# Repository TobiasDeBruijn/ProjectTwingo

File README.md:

# Project Twingo
I own a Renault Twingo Initiale from 2002. This car originally shipped with a simple FM radio, that wasn't enough.

## Goals
With this project I'm trying to do the following:
- Add Android Auto to the Twingo, both wireless and via USB
    - Retain the steering wheel controls
- Interior lighting
    - Replace ceiling light with LED
    - Feet of front passengers
- Replace the standard display in the middle of the dashboard? (Mine is sortof broken)
- Control AC electronically with a thermostat?

## License
All work in this project is licensed under the MIT license.

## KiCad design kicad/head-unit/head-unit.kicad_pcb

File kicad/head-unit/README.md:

# Head unit
The 'head unit' and all the required additional stuff

## head-unit
This is the main bit of the unit. This contains the STM32 microcontroller, the Raspberry Pi running Android Auto, the DAC and various controlling relays.

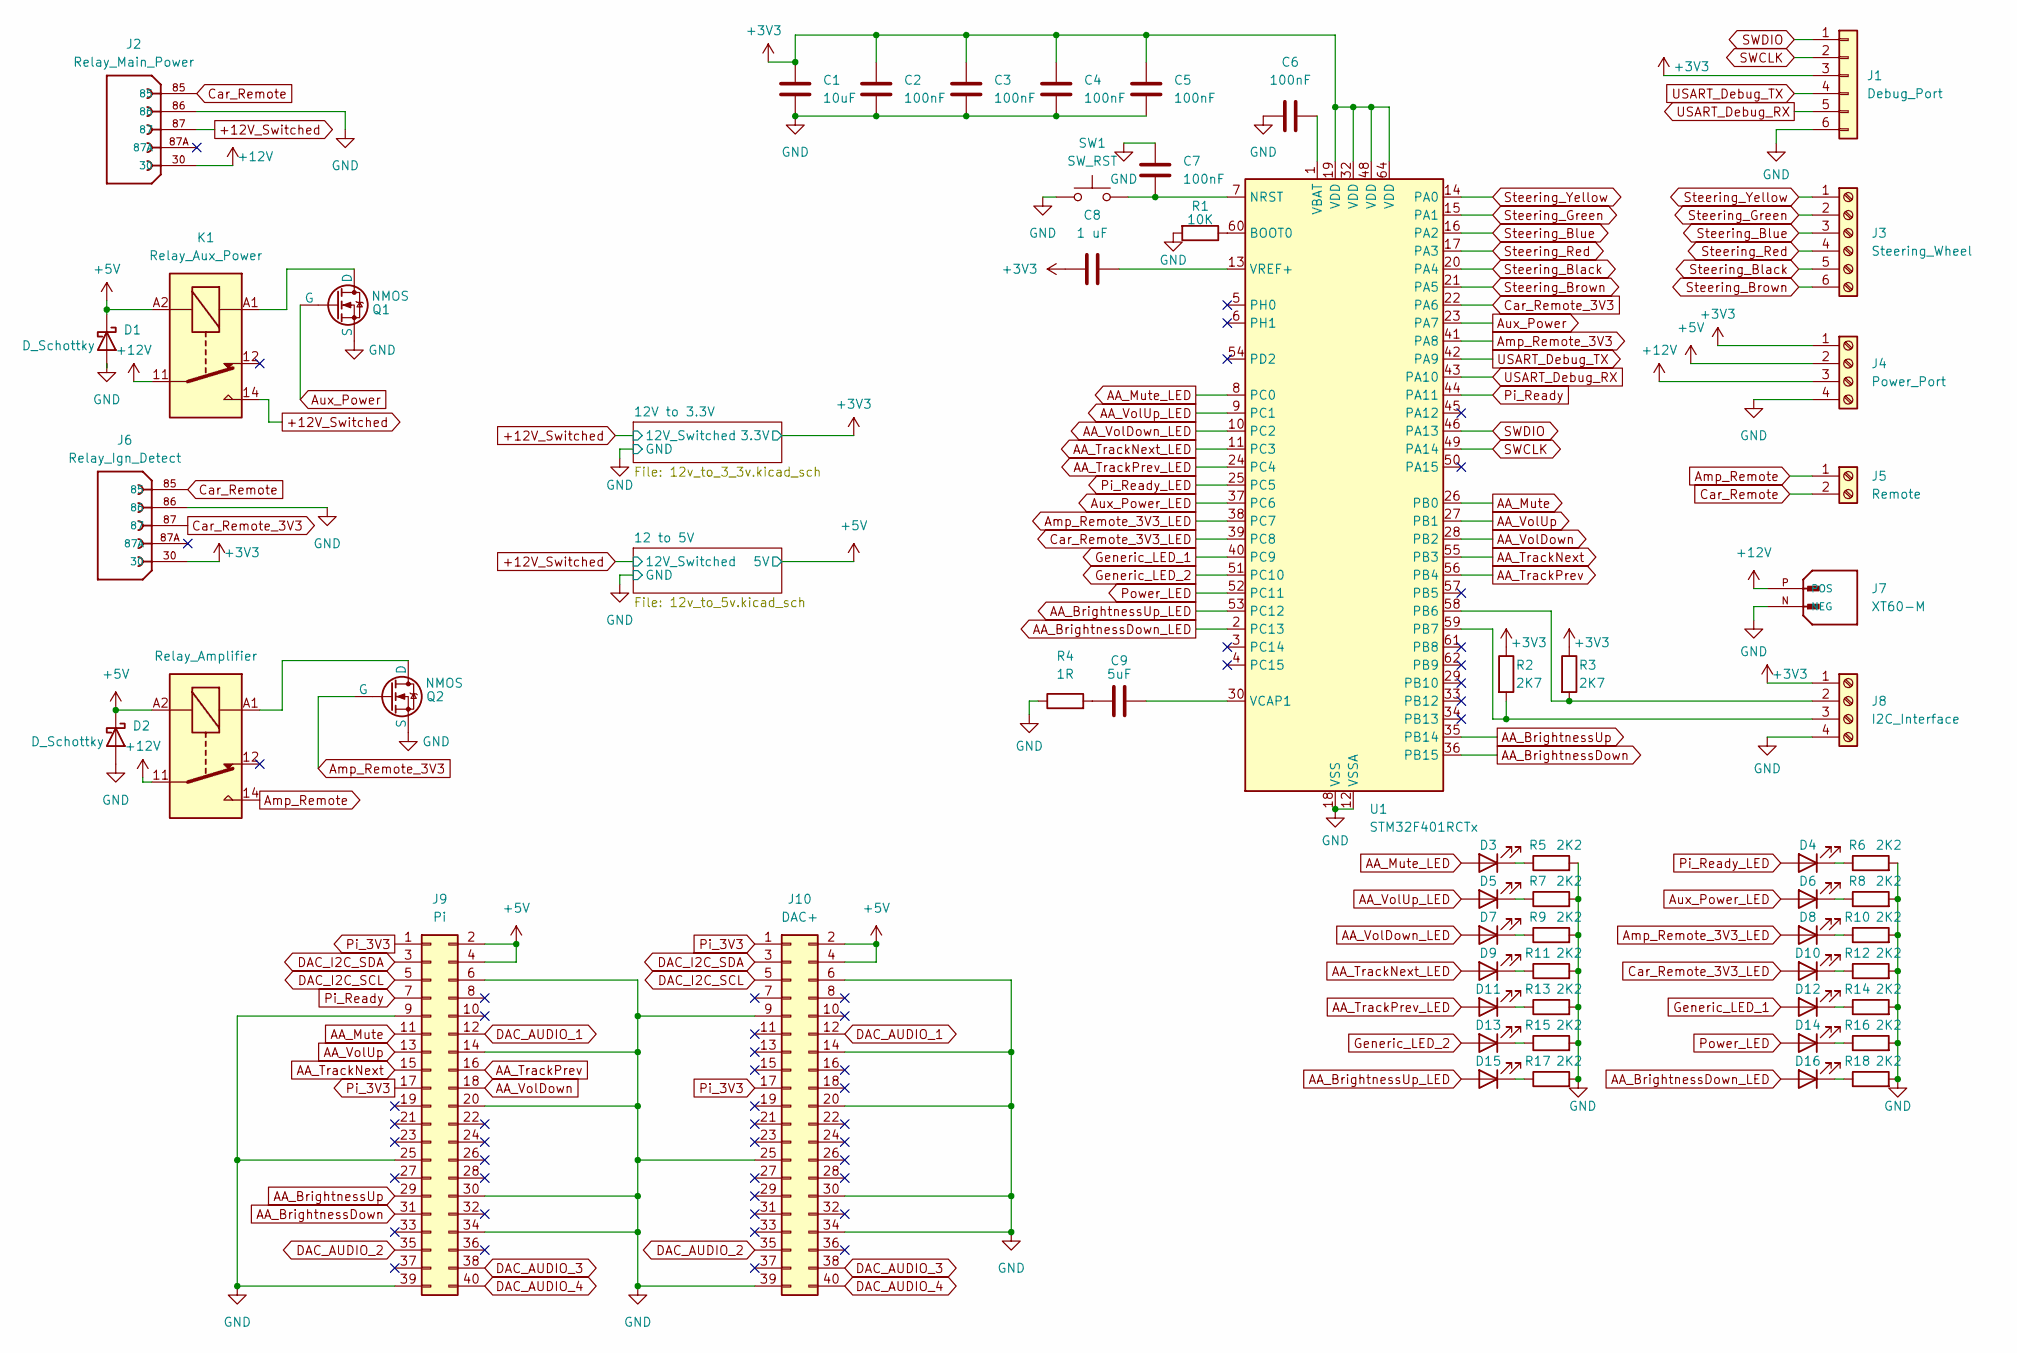
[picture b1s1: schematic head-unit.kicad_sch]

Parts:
C1: 10uF; C_0603_1608Metric
C2, C3, C4, C5, C6, C7: 100nF; C_0402_1005Metric
C8: 1 uF; C_0402_1005Metric
C9: 5uF; C_0603_1608Metric
D1, D2: D_Schottky; D_0603_1608Metric
D3, D4, D5, D6, D7, D8, D9, D10, D11, D12, D13, D14, D15, D16: LED; LED_0603_1608Metric
J1: Debug_Port; PinHeader_1x06_P2.54mm_Vertical
J2: Relay_Main_Power; TE_VCF4-1000; PARTREV B
J3: Steering_Wheel; TerminalBlock_bornier-6_P5.08mm
J4: Power_Port; TerminalBlock_bornier-4_P5.08mm
J5: Remote; TerminalBlock_bornier-2_P5.08mm
J6: Relay_Ign_Detect; TE_VCF4-1000; PARTREV B
J7: XT60-M; AMASS_XT60-M; PARTREV V1.2
J8: I2C_Interface; TerminalBlock_bornier-4_P5.08mm
J9: Pi; PinHeader_2x20_P2.54mm_Vertical
J10: DAC+; PinHeader_2x20_P2.54mm_Vertical
K1: Relay_Aux_Power; Relay_SPDT_Finder_36.11
K2: Relay_Amplifier; Relay_SPDT_Finder_36.11
Q1, Q2: NMOS; SW_SPDT_CK-JS102011SAQN
R1: 10K; R_0603_1608Metric
R2, R3: 2K7; R_0402_1005Metric
R4: 1R; R_0402_1005Metric
R5, R6, R7, R8, R9, R10, R11, R12, R13, R14, R15, R16, R17, R18: 2K2; R_0402_1005Metric
SW1: SW_RST; SW_Push_1P1T_NO_CK_KSC7xxJ
U1: STM32F401RCTx; LQFP-64_10x10mm_P0.5mm

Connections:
+3V3: C1.1, C2.1, C3.1, C4.1, C5.1, C8.2, J1.3, J4.1, J6.30, J8.1, R2.1, R3.1, U1.19 (VDD), U1.32 (VDD), U1.48 (VDD), U1.64 (VDD); also elsewhere on the board
+5V: D1.1 (K), D2.1 (K), J4.2, J9.2, J9.4, J10.2, J10.4, K1.A2, K2.A2; also elsewhere on the board
+12V: J2.30, J4.3, J7.P (POS), K1.11, K2.11
+12V_Switched: J2.87, K1.14; also elsewhere on the board
AA_BrightnessDown: J9.31, U1.36 (PB15)
AA_BrightnessDown_LED: D16.2 (A), U1.2 (PC13)
AA_BrightnessUp: J9.29, U1.35 (PB14)
AA_BrightnessUp_LED: D15.2 (A), U1.53 (PC12)
AA_Mute: J9.11, U1.26 (PB0)
AA_Mute_LED: D3.2 (A), U1.8 (PC0)
AA_TrackNext: J9.15, U1.55 (PB3)
AA_TrackNext_LED: D9.2 (A), U1.11 (PC3)
AA_TrackPrev: J9.16, U1.56 (PB4)
AA_TrackPrev_LED: D11.2 (A), U1.24 (PC4)
AA_VolDown: J9.18, U1.28 (PB2)
AA_VolDown_LED: D7.2 (A), U1.10 (PC2)
AA_VolUp: J9.13, U1.27 (PB1)
AA_VolUp_LED: D5.2 (A), U1.9 (PC1)
Amp_Remote: J5.1, K2.14
Amp_Remote_3V3: Q2.2 (G), U1.41 (PA8)
Amp_Remote_3V3_LED: D8.2 (A), U1.38 (PC7)
Aux_Power: Q1.2 (G), U1.23 (PA7)
Aux_Power_LED: D6.2 (A), U1.37 (PC6)
Car_Remote: J2.85, J5.2, J6.85
Car_Remote_3V3: J6.87, U1.22 (PA6)
Car_Remote_3V3_LED: D10.2 (A), U1.39 (PC8)
DAC_AUDIO_1: J9.12, J10.12
DAC_AUDIO_2: J9.35, J10.35
DAC_AUDIO_3: J9.38, J10.38
DAC_AUDIO_4: J9.40, J10.40
DAC_I2C_SCL: J9.5, J10.5
DAC_I2C_SDA: J9.3, J10.3
GND: C1.2, C2.2, C3.2, C4.2, C5.2, C6.1, C7.1, D1.2 (A), D2.2 (A), J1.6, J2.86, J4.4, J6.86, J7.N (NEG), J8.4, J9.6, J9.9, J9.14, J9.20, J9.25, J9.30, J9.34, J9.39, J10.6, J10.9, J10.14, J10.20, J10.25, J10.30, J10.34, J10.39, Q1.3 (S), Q2.3 (S), R1.2, R4.1, R5.2, R6.2, R7.2, R8.2, R9.2, R10.2, R11.2, R12.2, R13.2, R14.2, R15.2, R16.2, R17.2, R18.2, SW1.1, U1.12 (VSSA), U1.18 (VSS), U1.31 (VSS), U1.47 (VSS), U1.63 (VSS); also elsewhere on the board
Generic_LED_1: D12.2 (A), U1.40 (PC9)
Generic_LED_2: D13.2 (A), U1.51 (PC10)
unnamed: C9.2, R4.2
unnamed: D3.1 (K), R5.1
unnamed: D4.1 (K), R6.1
unnamed: D5.1 (K), R7.1
unnamed: D6.1 (K), R8.1
unnamed: D7.1 (K), R9.1
unnamed: D8.1 (K), R10.1
unnamed: D9.1 (K), R11.1
unnamed: D10.1 (K), R12.1
unnamed: D11.1 (K), R13.1
unnamed: D12.1 (K), R14.1
unnamed: D13.1 (K), R15.1
unnamed: D14.1 (K), R16.1
unnamed: D15.1 (K), R17.1
unnamed: D16.1 (K), R18.1
unnamed: J8.2, R3.2, U1.58 (PB6)
unnamed: J8.3, R2.2, U1.59 (PB7)
unnamed: K1.A1, Q1.1 (D)
unnamed: K2.A1, Q2.1 (D)
unnamed: R1.1, U1.60 (BOOT0)
unnamed: C7.2, SW1.2, U1.7 (NRST)
unnamed: C6.2, U1.1 (VBAT)
unnamed: C9.1, U1.30 (VCAP1)
unnamed: C8.1, U1.13 (VREF+)
Pi_3V3: J9.1, J9.17, J10.1, J10.17
Pi_Ready: J9.7, U1.44 (PA11)
Pi_Ready_LED: D4.2 (A), U1.25 (PC5)
Power_LED: D14.2 (A), U1.52 (PC11)
SWCLK: J1.2, U1.49 (PA14)
SWDIO: J1.1, U1.46 (PA13)
Steering_Black: J3.5, U1.20 (PA4)
Steering_Blue: J3.3, U1.16 (PA2)
Steering_Brown: J3.6, U1.21 (PA5)
Steering_Green: J3.2, U1.15 (PA1)
Steering_Red: J3.4, U1.17 (PA3)
Steering_Yellow: J3.1, U1.14 (PA0)
USART_Debug_RX: J1.5, U1.43 (PA10)
USART_Debug_TX: J1.4, U1.42 (PA9)

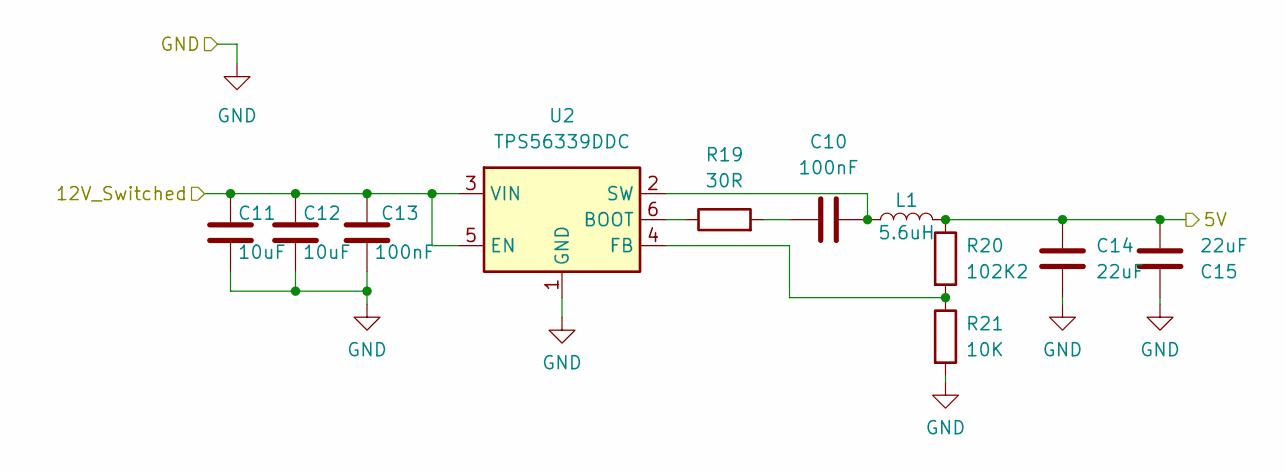
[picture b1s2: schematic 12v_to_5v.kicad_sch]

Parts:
C10, C13: 100nF; C_0402_1005Metric
C11, C12: 10uF; C_0603_1608Metric
C14, C15: 22uF; C_0603_1608Metric
L1: 5.6uH; L_6.3x6.3_H3
R19: 30R; R_0201_0603Metric
R20: 102K2; R_0805_2012Metric
R21: 10K; R_0603_1608Metric
U2: TPS56339DDC; SOT-23-6

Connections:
+5V: C14.1, C15.2, L1.2, R20.1; also elsewhere on the board
+12V_Switched: C11.1, C12.1, C13.1, U2.3 (VIN), U2.5 (EN); also elsewhere on the board
GND: C11.2, C12.2, C13.2, C14.2, C15.1, R21.2, U2.1 (GND); also elsewhere on the board
unnamed: C10.1, R19.2
unnamed: R19.1, U2.6 (BOOT)
unnamed: R20.2, R21.1, U2.4 (FB)
unnamed: C10.2, L1.1, U2.2 (SW)

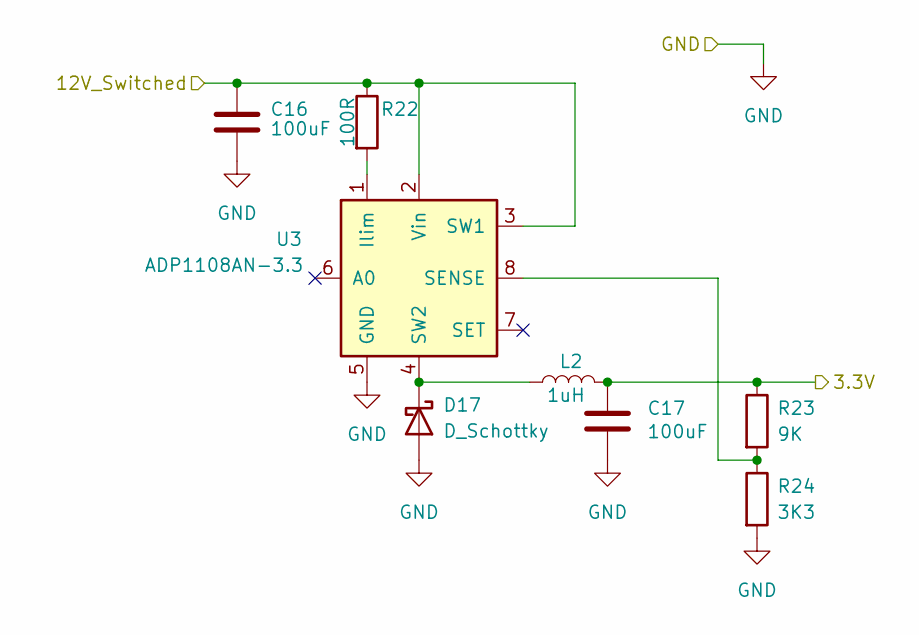
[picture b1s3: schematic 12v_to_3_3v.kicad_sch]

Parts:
C16, C17: 100uF; C_1206_3216Metric
D17: D_Schottky; D_0603_1608Metric
L2: 1uH; L_0402_1005Metric
R22: 100R; R_0402_1005Metric
R23: 9K; R_0603_1608Metric
R24: 3K3; R_0603_1608Metric
U3: ADP1108AN-3.3; DIP-8_W7.62mm

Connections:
+3V3: C17.1, L2.2, R23.1; also elsewhere on the board
+12V_Switched: C16.1, R22.1, U3.2 (Vin), U3.3 (SW1); also elsewhere on the board
GND: C16.2, C17.2, D17.2 (A), R24.2, U3.5 (GND); also elsewhere on the board
unnamed: D17.1 (K), L2.1, U3.4 (SW2)
unnamed: R22.2, U3.1 (Ilim)
unnamed: R23.2, R24.1, U3.8 (SENSE)

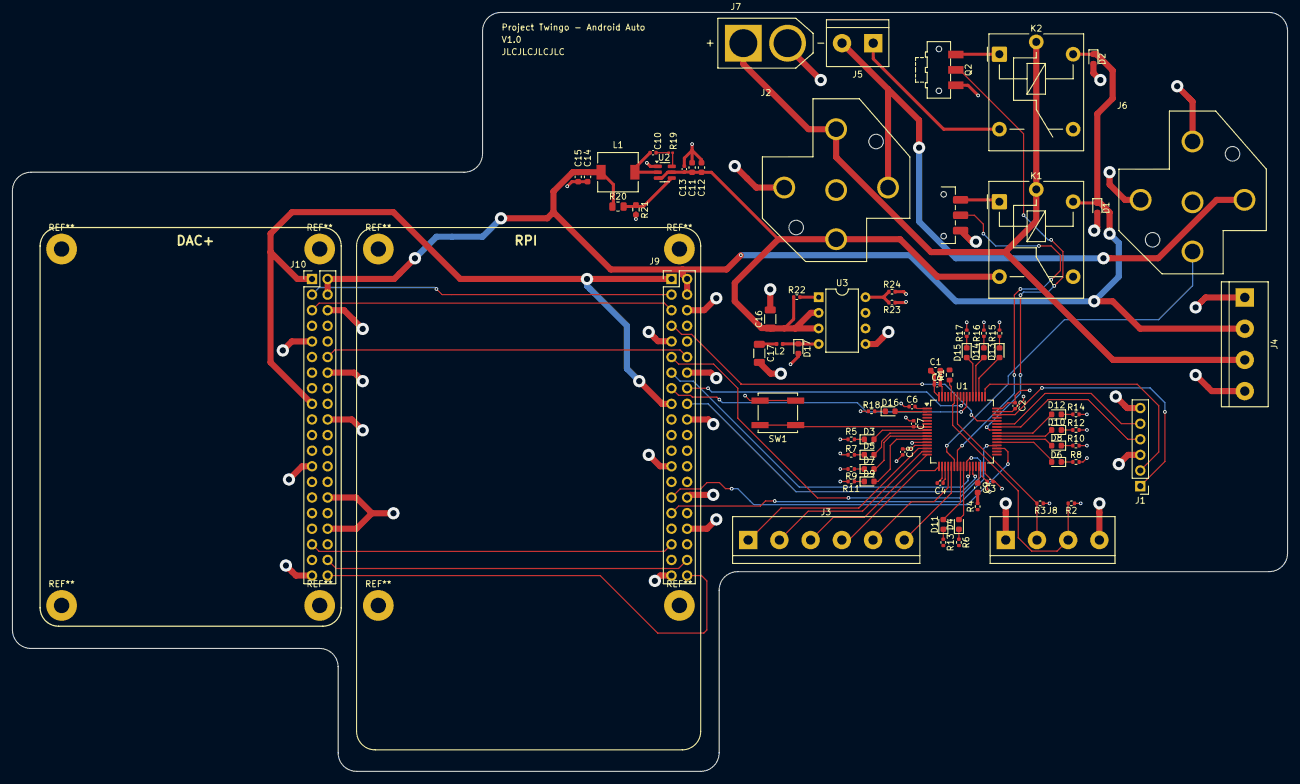
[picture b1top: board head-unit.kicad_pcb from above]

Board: 4 copper layers, 207.5 x 123.5 mm, 78 parts (0 on the bottom side), 80 nets.

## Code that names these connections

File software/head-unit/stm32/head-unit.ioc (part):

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Mcu.Name=STM32L151C(6-8-B)TxA
Mcu.Package=LQFP48
Mcu.UserName=STM32L151C6TxA
PA0-WKUP1.GPIOParameters=GPIO_Label
PA0-WKUP1.GPIO_Label=Debug_LED
PA0-WKUP1.Signal=GPIO_Output
PA1.GPIOParameters=GPIO_Label
PA1.GPIO_Label=Volume_Up
PA1.Signal=GPIO_Output
PA10.Mode=Asynchronous
PA10.Signal=USART1_RX
PA11.GPIOParameters=GPIO_Label
PA11.GPIO_Label=Volume_Mute
PA11.Signal=GPIO_Output
PA13.GPIOParameters=GPIO_Label
PA13.GPIO_Label=Programmer_DIO
PA13.Signal=SYS_JTMS-SWDIO
PA14.GPIOParameters=GPIO_Label
PA14.GPIO_Label=Programmer_CLK
PA14.Signal=SYS_JTCK-SWCLK
PA2.GPIOParameters=GPIO_Label
PA2.GPIO_Label=Volume_Down
PA2.Signal=GPIO_Output
PA3.GPIOParameters=GPIO_Label
PA3.GPIO_Label=Track_Next
PA3.Signal=GPIO_Output
PA4.Mode=NSS_Signal_Hard_Output
PA4.Signal=SPI1_NSS
PA5.Mode=Full_Duplex_Master
PA5.Signal=SPI1_SCK
PA6.Mode=Full_Duplex_Master
PA6.Signal=SPI1_MISO
PA7.Mode=Full_Duplex_Master
PA7.Signal=SPI1_MOSI
PA9.Mode=Asynchronous
PA9.Signal=USART1_TX
PB0.GPIOParameters=GPIO_Label
PB0.GPIO_Label=Stereo_Remote
PB0.Signal=GPIO_Output
PB1.GPIOParameters=GPIO_Label
PB1.GPIO_Label=Secondary_Power
PB1.Signal=GPIO_Output
PB10.GPIOParameters=GPIO_Label
PB10.GPIO_Label=Debug_UART_TX
PB10.Mode=Asynchronous
PB10.Signal=USART3_TX
PB11.GPIOParameters=GPIO_Label
PB11.GPIO_Label=Debug_UART_RX
PB11.Mode=Asynchronous
PB11.Signal=USART3_RX
PB12.GPIOParameters=GPIO_PuPd,GPIO_Label
PB12.GPIO_Label=Steering_Wheel_Red
PB12.GPIO_PuPd=GPIO_PULLUP
PB12.Signal=GPIO_Input
PB13.GPIOParameters=GPIO_Label
PB13.GPIO_Label=Steering_Wheel_Green
PB13.Signal=GPIO_Output
PB14.GPIOParameters=GPIO_Label
PB14.GPIO_Label=Steering_Wheel_Yellow
PB14.Signal=GPIO_Output
PB15.GPIOParameters=GPIO_PuPd,GPIO_Label
PB15.GPIO_Label=Steering_Wheel_Brown
PB15.GPIO_PuPd=GPIO_PULLUP
PB15.Signal=GPIO_Input
PB2.GPIOParameters=GPIO_Label
PB2.GPIO_Label=Remote_Detect
PB2.Signal=GPIO_Input
PB8.GPIOParameters=GPIO_PuPd,GPIO_Label
PB8.GPIO_Label=Steering_Wheel_Black
PB8.GPIO_PuPd=GPIO_PULLUP
PB8.Signal=GPIO_Input
PB9.GPIOParameters=GPIO_Label
PB9.GPIO_Label=Steering_Wheel_Blue
PB9.Signal=GPIO_Output
RCC.HSE_VALUE=24000000
RCC.SYSCLKFreq_VALUE=24000000
RCC.SYSCLKSource=RCC_SYSCLKSOURCE_PLLCLK
board=custom

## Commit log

2024-02-14 Initial commit: - WIP Head unit Kicad files - WIP Head unit STM firmware
2024-02-14 Relays, cleanup
2024-04-18 Work on head unit
2024-04-18 Initial work on headunit
2024-04-18 Kicad changes
2024-04-19 Dankje Douwe
2024-04-19 Fix mosfets, switch to screw terminals and XT60
2024-04-20 Add I2C, begin routing
2024-04-20 Save
2024-04-24 WIP routing
2024-04-24 More routing
2024-04-29 Fix pi moutning holes?
2024-04-29 Stuff
2024-04-29 Routing to pi
2024-04-30 Outline for DAC+; board outline
